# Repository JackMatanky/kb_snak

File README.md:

# SNAK: Sisyphus Needed a Keyboard

## Credits

- The first version would not have been possible without [flatfootfox's](https://github.com/ImStuBTW) [Let's Design a Keyboard With Ergogen](https://flatfootfox.com/ergogen-introduction/) guide.
- Later versions were heavily inspired by [ceolide's](https://github.com/ceoloide) [corney-island](https://github.com/ceoloide/corney-island)
- Almost all footprints are from [infused-kim](https://github.com/infused-kim/kb_ergogen_fp)

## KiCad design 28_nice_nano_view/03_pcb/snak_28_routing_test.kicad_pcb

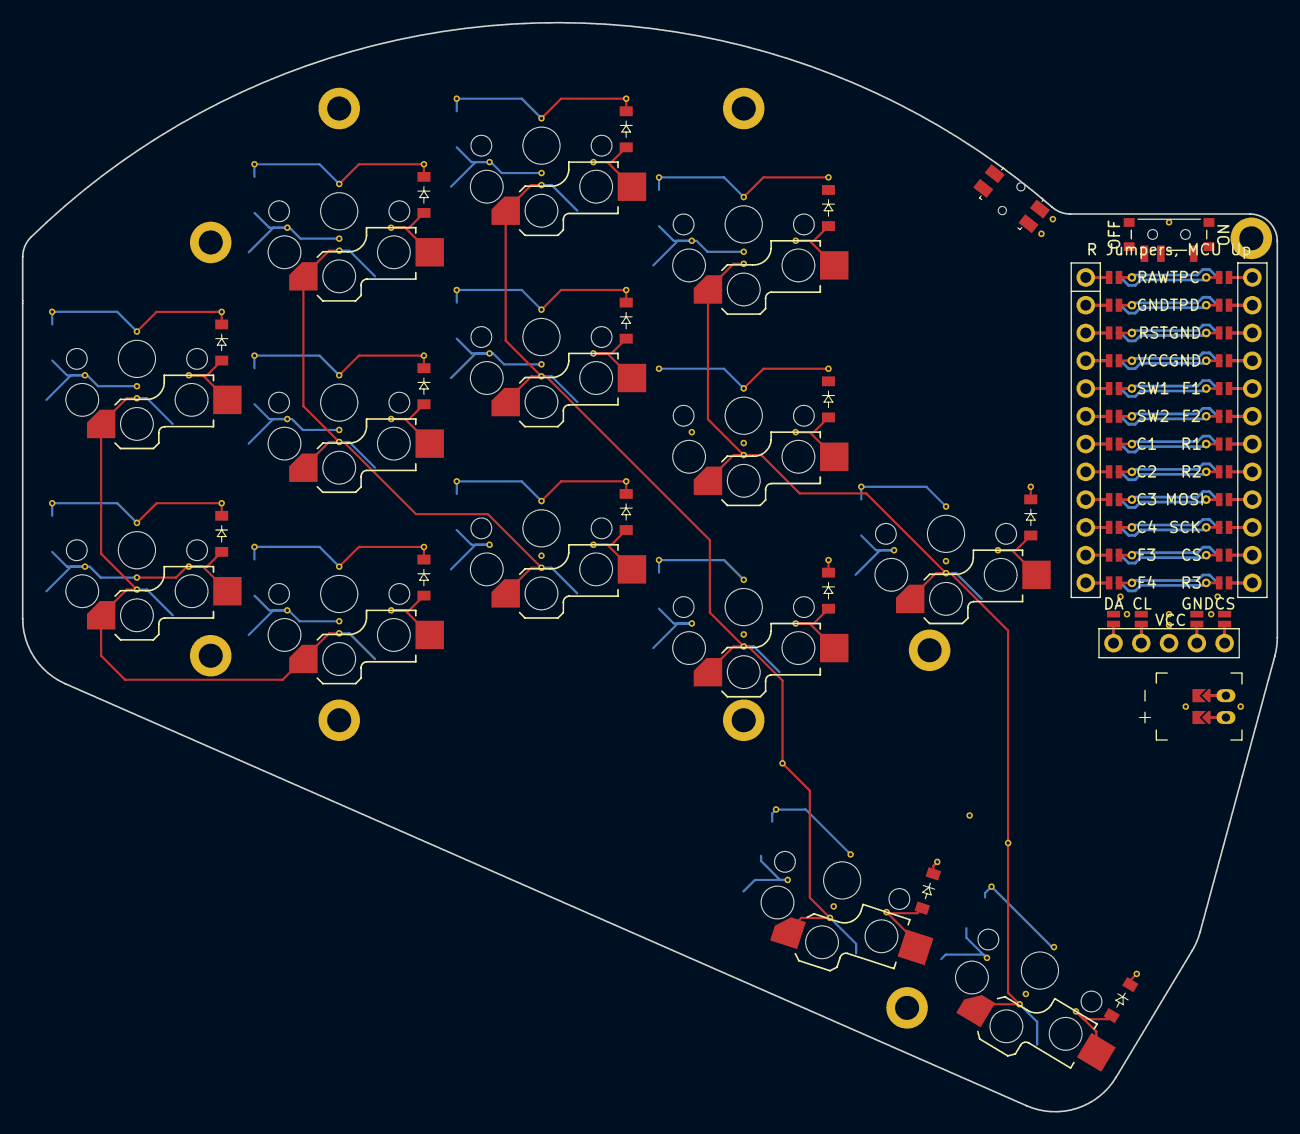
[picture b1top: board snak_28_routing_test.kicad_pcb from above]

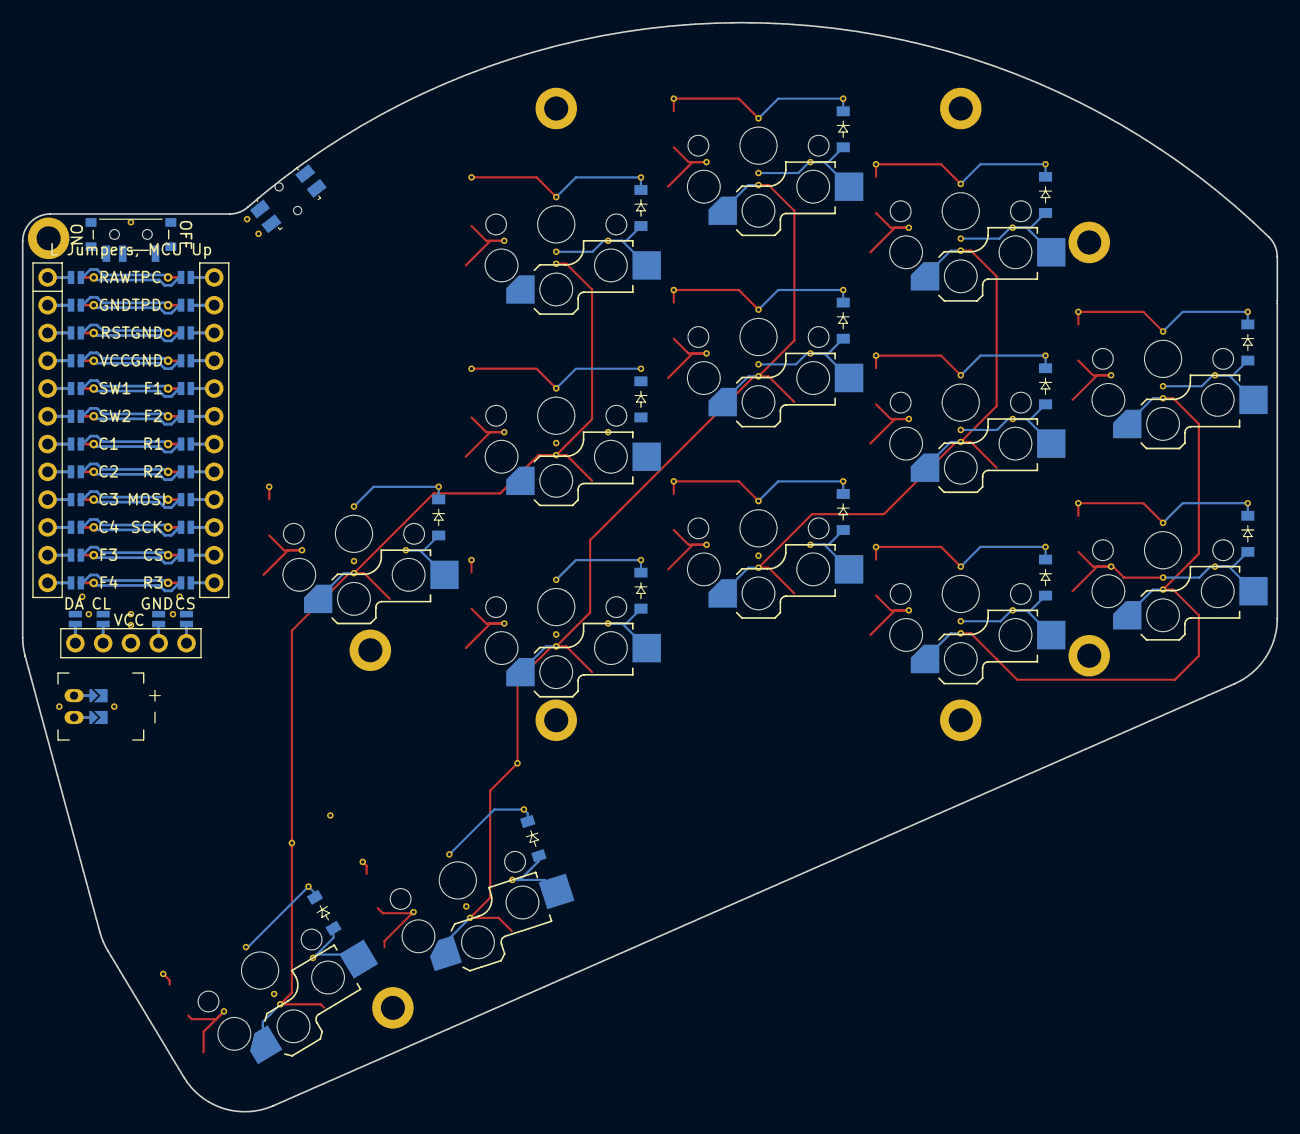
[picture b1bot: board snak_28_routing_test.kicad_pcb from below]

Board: 2 copper layers, 114.8 x 99.6 mm, 56 parts (28 on the bottom side), 48 nets.

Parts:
D1, D2, D3, D4, D5, D6, D7, D8, D9, D10, D11, D12, D13, D14, D15, D16, D17, D18, D19, D20, D21, D22, D23, D24, D25, D26, D27, D28: diode_tht_sod123
DISP1: display_nice_view
H1, H2, H3, H4, H5, H6, H7, H8, H9: mounting_hole_plated
JST1: battery_connector_jst_ph_2
MCU1: mcu_nice_nano
PWR1: power_switch_smd_side
RST1: reset_switch_smd_side
S1, S2, S3, S4, S5, S6, S7, S8, S9, S10, S11, S12, S13, S14: switch_choc_v1_v2

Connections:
C1: MCU1.118, S1.1, S2.1, S3.1
C2: MCU1.117, S4.1, S5.1, S6.1
C3: MCU1.116, S7.1, S8.1, S9.1, S13.1
C4: MCU1.115, S10.1, S11.1, S12.1, S14.1
CS: DISP1.14, DISP1.24, MCU1.111
DISP1_1: DISP1.1, DISP1.10, DISP1.23
DISP1_2: DISP1.2, DISP1.11, DISP1.22
DISP1_4: DISP1.4, DISP1.12, DISP1.21
DISP1_5: DISP1.5, DISP1.13, DISP1.20
GND: DISP1.15, DISP1.25, JST1.2, MCU1.103, MCU1.104, MCU1.123, RST1.1, RST1.3
JST1_1: JST1.11, JST1.21, JST1.31
JST1_2: JST1.12, JST1.22, JST1.32
MCU1_1: MCU1.1, MCU1.24
MCU1_2: MCU1.2, MCU1.23
MCU1_3: MCU1.3, MCU1.22
MCU1_4: MCU1.4, MCU1.21
MCU1_5: MCU1.5, MCU1.20
MCU1_6: MCU1.6, MCU1.19
MCU1_7: MCU1.7, MCU1.18
MCU1_8: MCU1.8, MCU1.17
MCU1_9: MCU1.9, MCU1.16
MCU1_10: MCU1.10, MCU1.15
MCU1_11: MCU1.11, MCU1.14
MCU1_12: MCU1.12, MCU1.13
MOSI: DISP1.17, DISP1.27, MCU1.109
R1: D2.1, D5.1, D8.1, D11.1, D16.1, D19.1, D22.1, D25.1, MCU1.107
R2: D1.1, D4.1, D7.1, D10.1, D12.1, D15.1, D18.1, D21.1, D24.1, D26.1, MCU1.108
R3: D3.1, D6.1, D9.1, D17.1, D20.1, D23.1, MCU1.112
R4: D13.1, D14.1, D27.1, D28.1
RAW: MCU1.124, PWR1.2
RST: MCU1.122, RST1.2, RST1.4
SCK: DISP1.16, DISP1.26, MCU1.110
VCC: DISP1.3, MCU1.121
in_home: D14.2, D28.2, S14.2
index_bot: D9.2, D23.2, S9.2
index_mid: D10.2, D24.2, S10.2
index_top: D11.2, D25.2, S11.2
inner_mid: D12.2, D26.2, S12.2
middle_bot: D6.2, D20.2, S6.2
middle_mid: D7.2, D21.2, S7.2
middle_top: D8.2, D22.2, S8.2
out_home: D13.2, D27.2, S13.2
pinky_mid: D1.2, D15.2, S1.2
pinky_top: D2.2, D16.2, S2.2
pos: JST1.1, PWR1.1, PWR1.3
ring_bot: D3.2, D17.2, S3.2
ring_mid: D4.2, D18.2, S4.2
ring_top: D5.2, D19.2, S5.2

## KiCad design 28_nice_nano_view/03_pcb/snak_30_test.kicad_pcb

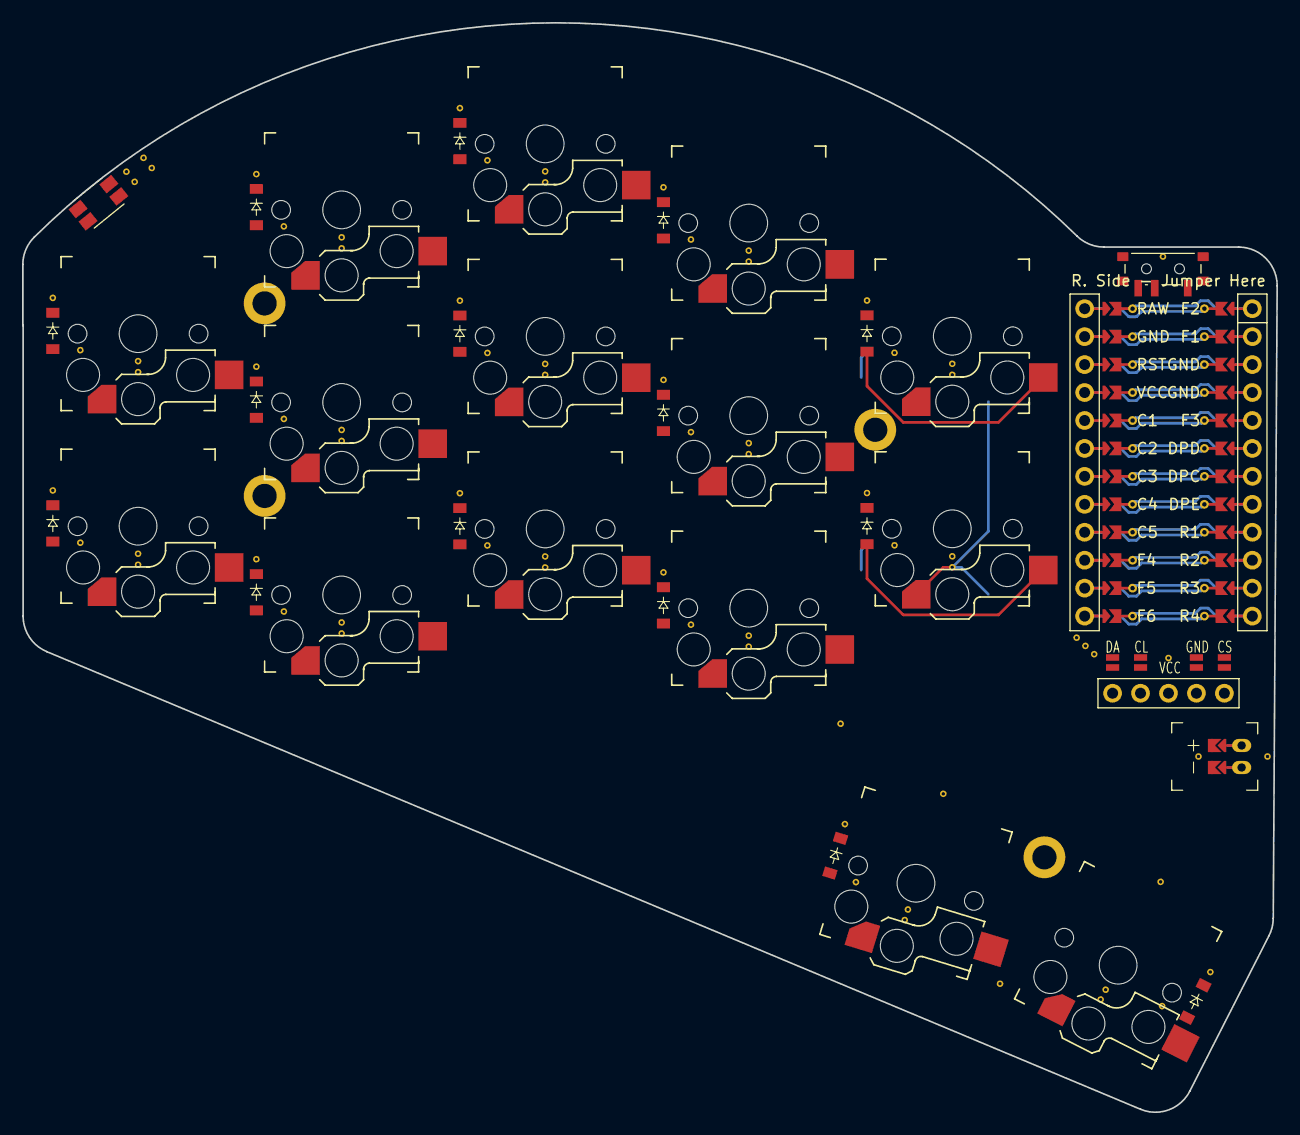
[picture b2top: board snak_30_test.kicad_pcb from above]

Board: 2 copper layers, 114.0 x 99.0 mm, 39 parts (0 on the bottom side), 38 nets.

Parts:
D1, D2, D3, D4, D5, D6, D7, D8, D9, D10, D11, D12, D13, D14, D15: ComboDiode
DISP1: nice!view
H1, H2, H3, H4: mounting_hole
JST1: JST_PH_S2B-PH-K
MCU1: nice_nano
S1, S2, S3, S4, S5, S6, S7, S8, S9, S10, S11, S12, S13, S14, S15: PG1350
SW1: power_switch
SW2: sw_reset_side

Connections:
C1: MCU1.5, S1.1, S2.1, S3.1
C2: MCU1.6, S4.1, S5.1, S6.1
C3: MCU1.7, S7.1, S8.1, S9.1
C4: MCU1.8, S10.1, S11.1, S14.1
C5: MCU1.9, S12.1, S13.1, S15.1
DISP1_1: DISP1.1, DISP1.10, DISP1.23
DISP1_2: DISP1.2, DISP1.11, DISP1.22
DISP1_4: DISP1.4, DISP1.12, DISP1.21
DISP1_5: DISP1.5, DISP1.13, DISP1.20
DPC: DISP1.15, DISP1.25, MCU1.118
DPD: DISP1.14, DISP1.24, MCU1.119
DPE: DISP1.17, DISP1.27, MCU1.117
GND: DISP1.16, DISP1.26, JST1.1, MCU1.2, MCU1.121, MCU1.122, SW2.1
JST1_1: JST1.11, JST1.21, JST1.31
JST1_2: JST1.12, JST1.22, JST1.32
R1: D2.1, D5.1, D8.1, D11.1, D13.1, MCU1.116
R2: D1.1, D4.1, D7.1, D10.1, D12.1, MCU1.115
R3: D3.1, D6.1, D9.1, MCU1.114
R4: D14.1, D15.1, MCU1.113
RAW: MCU1.1, SW1.3, SW1.6
RST: MCU1.3, SW2.2
VCC: DISP1.3, MCU1.4
in_home: D15.2, S15.2
index_bot: D9.2, S9.2
index_mid: D10.2, S10.2
index_top: D11.2, S11.2
inner_mid: D12.2, S12.2
inner_top: D13.2, S13.2
middle_bot: D6.2, S6.2
middle_mid: D7.2, S7.2
middle_top: D8.2, S8.2
out_home: D14.2, S14.2
pinky_mid: D1.2, S1.2
pinky_top: D2.2, S2.2
pos: JST1.2, SW1.2, SW1.5
ring_bot: D3.2, S3.2
ring_mid: D4.2, S4.2
ring_top: D5.2, S5.2

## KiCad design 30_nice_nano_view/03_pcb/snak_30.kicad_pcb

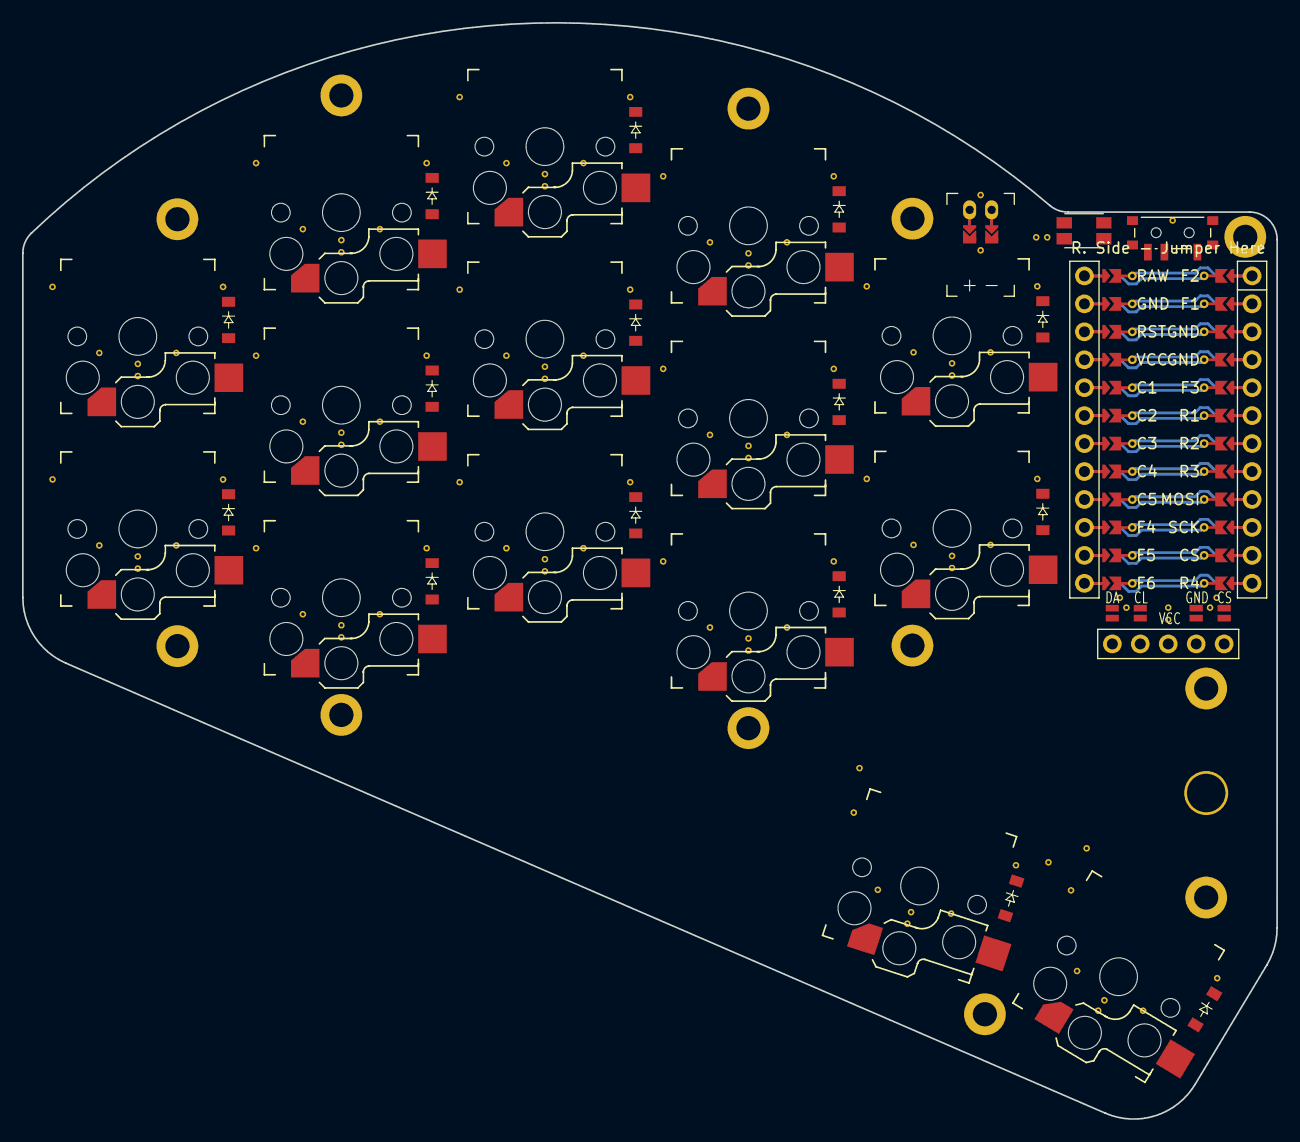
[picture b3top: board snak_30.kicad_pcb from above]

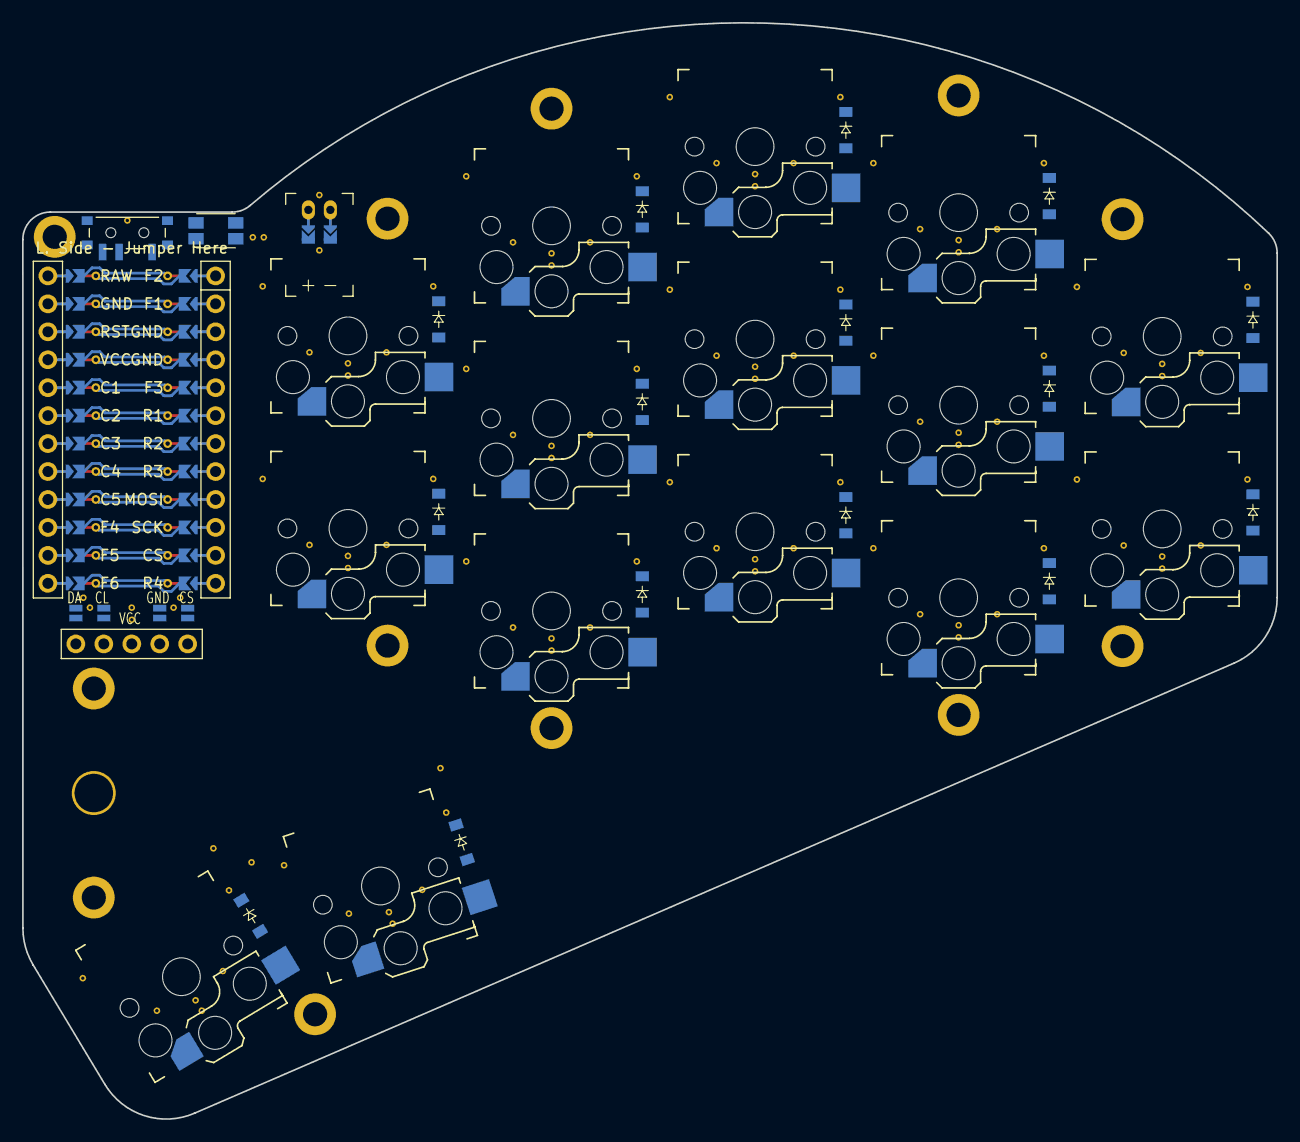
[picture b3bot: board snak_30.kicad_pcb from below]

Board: 2 copper layers, 114.0 x 99.6 mm, 61 parts (15 on the bottom side), 38 nets.

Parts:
D1, D2, D3, D4, D5, D6, D7, D8, D9, D10, D11, D12, D13, D14, D15, D16, D17, D18, D19, D20, D21, D22, D23, D24, D25, D26, D27, D28, D29, D30: diode_tht_sod123
DISP1: nice!view
H1, H2, H3, H4, H5, H6, H7, H8, H9, H10: mounting_hole
JST1: JST_PH_S2B-PH-K
MCU1: nice_nano
S1, S2, S3, S4, S5, S6, S7, S8, S9, S10, S11, S12, S13, S14, S15: PG1350
SW1: power_switch
SW2: sw_reset_side
TP1: trackpoint_mount_t430

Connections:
C1: MCU1.5, S1.1, S2.1
C2: MCU1.6, S3.1, S4.1, S5.1
C3: MCU1.7, S6.1, S7.1, S8.1
C4: MCU1.8, S9.1, S10.1, S11.1, S14.1
C5: MCU1.9, S12.1, S13.1, S15.1
CS: DISP1.17, DISP1.27, MCU1.114
DISP1_1: DISP1.1, DISP1.10, DISP1.23
DISP1_2: DISP1.2, DISP1.11, DISP1.22
DISP1_4: DISP1.4, DISP1.12, DISP1.21
DISP1_5: DISP1.5, DISP1.13, DISP1.20
GND: DISP1.16, DISP1.26, JST1.1, MCU1.2, MCU1.121, MCU1.122, SW2.1
JST1_1: JST1.11, JST1.21, JST1.31
JST1_2: JST1.12, JST1.22, JST1.32
MOSI: DISP1.14, DISP1.24, MCU1.116
R1: D2.1, D5.1, D8.1, D11.1, D13.1, D17.1, D20.1, D23.1, D26.1, D28.1, MCU1.119
R2: D1.1, D4.1, D7.1, D10.1, D12.1, D16.1, D19.1, D22.1, D25.1, D27.1, MCU1.118
R3: D3.1, D6.1, D9.1, D18.1, D21.1, D24.1, MCU1.117
R4: D14.1, D15.1, D29.1, D30.1, MCU1.113
RAW: MCU1.1, SW1.3, SW1.6
RST: MCU1.3, SW2.2
SCK: DISP1.15, DISP1.25, MCU1.115
VCC: DISP1.3, MCU1.4
in_home: D15.2, D30.2, S15.2
index_bot: D9.2, D24.2, S9.2
index_mid: D10.2, D25.2, S10.2
index_top: D11.2, D26.2, S11.2
inner_mid: D12.2, D27.2, S12.2
inner_top: D13.2, D28.2, S13.2
middle_bot: D6.2, D21.2, S6.2
middle_mid: D7.2, D22.2, S7.2
middle_top: D8.2, D23.2, S8.2
out_home: D14.2, D29.2, S14.2
pinky_mid: D1.2, D16.2, S1.2
pinky_top: D2.2, D17.2, S2.2
pos: JST1.2, SW1.2, SW1.5
ring_bot: D3.2, D18.2, S3.2
ring_mid: D4.2, D19.2, S4.2
ring_top: D5.2, D20.2, S5.2

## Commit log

2024-01-03 add mounting holes to pcb
2024-01-04 changed the top and bottom curves to a single polygon
2024-01-04 Create LICENSE
2024-01-07 add via for oled gnd
2024-01-07 config file with circle intersect
2024-01-07 update config with circle intersect
2024-01-08 kicad to pcb
2024-01-10 final board
2024-01-15 finish kb_snak ergogen, pcb routing, and gerber
2024-01-16 update repo structure
2024-01-22 update before moving files
2024-02-09 start working on case
2024-02-15 consolidate v1 files in single directory
2024-02-20 add thirty key config
2024-02-21 add 30 key layout and update paths and thumb cluster
2024-02-22 add xiao ble info
2024-02-23 move xiao related files to dedicated directory
2024-02-24 update 30 key layouts
2024-02-24 update thumb spacing
2024-02-26 start working on thirty key pcb
2024-02-27 place number of keys before mcu
2024-02-29 add info about trackpoint
2024-02-29 add infused-kim ergogen helper
2024-02-29 add round bottom to pcb
2024-02-29 update 30 key nicenano board
2024-03-01 add config file to xiao 34
2024-03-03 add ergopad img
2024-03-04 update to add space between mcu and thumb
2024-03-06 move mcu mount hole further right
2024-03-06 update config and move reset and jst to on top of mcu
2024-03-12 add choc switch and hotswap specification images
2024-03-12 test xiao fp
2024-03-14 update footprints
2024-03-19 add cirque datasheet
2024-03-20 add 23331_2 config
2024-03-21 update 28 key config
2024-03-25 add scrollwheel to 28 key config
2024-03-25 update scrollwheel rotation and placement
2024-03-26 update 28
2024-03-27 update 28 config
2024-03-28 update 28 key tags
2024-03-28 add traces lib
2024-03-31 test scrollwheel footprint
2024-03-31 test trackpoint footprints
2024-07-03 added a project for a unibody board
2024-07-05 update unibody
2024-07-13 add presets to unibody
2024-08-01 kicad files
2024-08-01 add cli config
2024-08-10 unify naming conventions between unibody and split snak_28
2024-08-10 update pin definition on snak 28 split
2024-08-14 kicad routing test with minimal pin usage without a thumb row pin
2024-09-20 work on scrollwheel
2024-11-07 renamed trackpoint pinout images to match their version
2025-03-07 add gitignore
2025-06-12 update config cli to gui
2025-06-12 add gui for 30 keys
2025-06-12 add gui for 30 keys and one diode
